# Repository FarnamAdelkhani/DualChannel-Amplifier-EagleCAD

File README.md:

# DualChannel-Amplifier-EagleCAD
Design amplifier design in Eagle, then export Gerber files for printing. Order components and solder away.

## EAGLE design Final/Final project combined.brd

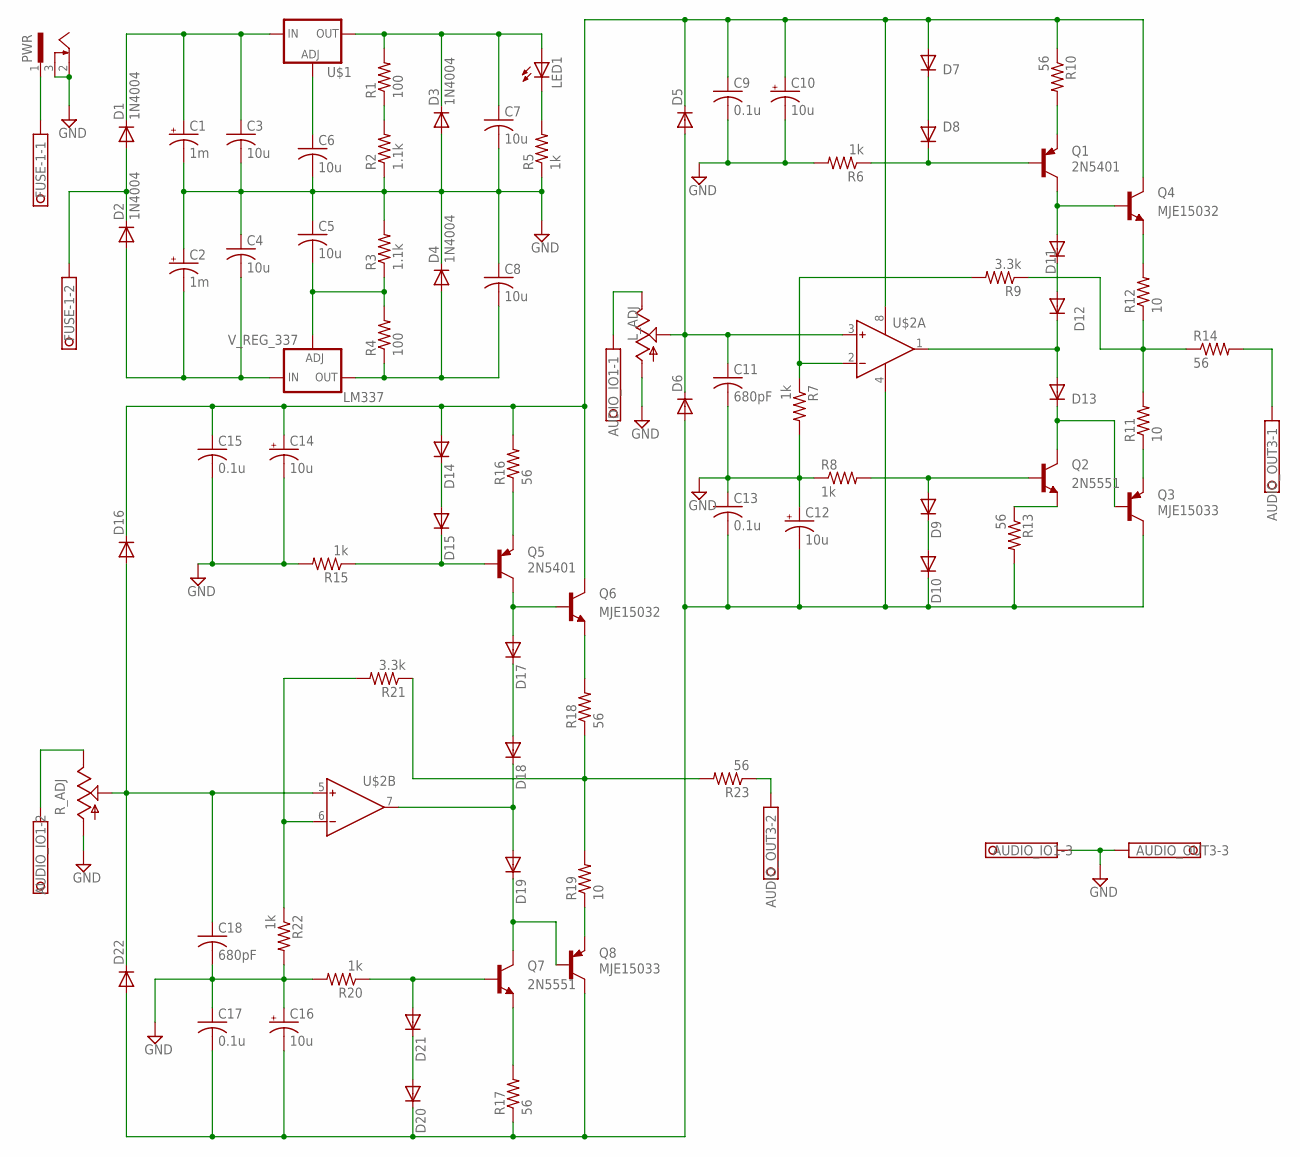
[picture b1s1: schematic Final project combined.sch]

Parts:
AUDIO_IO1: 1751251
AUDIO_OUT3: 1751251
C1, C2: 1m; E2-5
C3, C4, C5, C6, C7, C8: 10u; C025-024X044
C9, C13, C15, C17: 0.1u; C025-024X044
C10, C12, C14, C16: 10u; E2-5
C11, C18: 680pF; C025-024X044
D1, D2, D3, D4, D14, D15, D16, D17, D18, D19, D20, D21, D22: 1N4004; DO41-10
D5, D6, D7, D8, D9, D10, D11, D12, D13: 1N4148DO35-7; DO35-7
FUSE-1: 1751248
LED1: LED5MM
LM337: V_REG_337; TO220-ADJ-NEG
L_ADJ: TRIM_US-B64Y; B64Y
PWR: SCD-014A; SCD-014-A
Q1, Q5: 2N5401
Q2, Q7: 2N5551
Q3, Q8: MJE15033; TO220V
Q4, Q6: MJE15032; TO220V
R1, R4: 100; 0207/15
R2, R3: 1.1k; 0207/15
R5, R6, R7, R8, R15, R20, R22: 1k; 0207/15
R9, R21: 3.3k; 0207/15
R10, R13, R14, R16, R17, R18, R23: 56; 0207/15
R11, R12, R19: 10; 0207/15
R_ADJ: TRIM_US-B64Y; B64Y
U$1: V_REG_317SINK; TO220-ADJ
U$2: OP275'P'; DIL08

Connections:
GND: AUDIO_IO1.3, AUDIO_OUT3.3, C1.-, C2.+, C3.2, C4.1, C5.1, C6.2, C7.2, C8.1, C9.2, C10.-, C11.2, C12.+, C13.1, C14.-, C15.2, C16.+, C17.1, C18.2, D3.A, D4.C, L_ADJ.A, PWR.2, PWR.3, R2.1, R3.2, R5.1, R6.2, R7.2, R8.1, R15.2, R20.2, R22.2, R_ADJ.A
unnamed: D7.C, D8.A
unnamed: R1.1, R2.2
unnamed: C11.1, D5.A, D6.C, L_ADJ.S, U$2.3 (IN+)
unnamed: D11.A, Q1.C, Q4.1 (B)
unnamed: C9.1, C10.+, C14.+, C15.1, D5.C, D7.A, D14.A, D16.C, Q4.2 (C), Q6.2 (C), R10.1, R16.2, U$2.8 (V+)
unnamed: D11.C, D12.A
unnamed: D1.A, D2.C, FUSE-1.2
unnamed: D17.A, Q5.C, Q6.1 (B)
unnamed: C2.-, C4.2, D2.A, LM337.IN
unnamed: C1.+, C3.1, D1.C, U$1.IN
unnamed: D8.C, Q1.B, R6.1
unnamed: R7.1, R9.2, U$2.2 (IN-)
unnamed: D9.A, Q2.B, R8.2
unnamed: D9.C, D10.A
unnamed: Q2.E, R13.1
unnamed: D13.C, Q2.C, Q3.1 (B)
unnamed: D12.C, D13.A, U$2.1 (OUT)
unnamed: R9.1, R11.2, R12.1, R14.1
unnamed: Q3.3 (E), R11.1
unnamed: Q4.3 (E), R12.2
unnamed: C6.1, U$1.ADJ
unnamed: Q1.E, R10.2
unnamed: FUSE-1.1, PWR.1
unnamed: D14.C, D15.A
unnamed: D15.C, Q5.B, R15.1
unnamed: Q5.E, R16.1
unnamed: Q6.3 (E), R18.2
unnamed: D17.C, D18.A
unnamed: Q8.3 (E), R19.1
unnamed: D19.C, Q7.C, Q8.1 (B)
unnamed: D18.C, D19.A, U$2.7 (OUT)
unnamed: D21.A, Q7.B, R20.1
unnamed: D20.A, D21.C
unnamed: R18.1, R19.2, R21.1, R23.2
unnamed: R21.2, R22.1, U$2.6 (IN-)
unnamed: C18.1, D16.A, D22.C, R_ADJ.S, U$2.5 (IN+)
unnamed: Q7.E, R17.2
unnamed: AUDIO_IO1.2, R_ADJ.E
unnamed: C12.-, C13.2, C16.-, C17.2, D6.A, D10.C, D20.C, D22.A, Q3.2 (C), Q8.2 (C), R13.2, R17.1, U$2.4 (V-)
unnamed: AUDIO_IO1.1, L_ADJ.E
unnamed: C8.2, D4.A, LM337.OUT, R4.1
unnamed: C5.2, LM337.ADJ, R3.1, R4.2
unnamed: LED1.K (C), R5.2
unnamed: C7.1, D3.C, LED1.A, R1.2, U$1.OUT
unnamed: AUDIO_OUT3.2, R23.1
unnamed: AUDIO_OUT3.1, R14.2

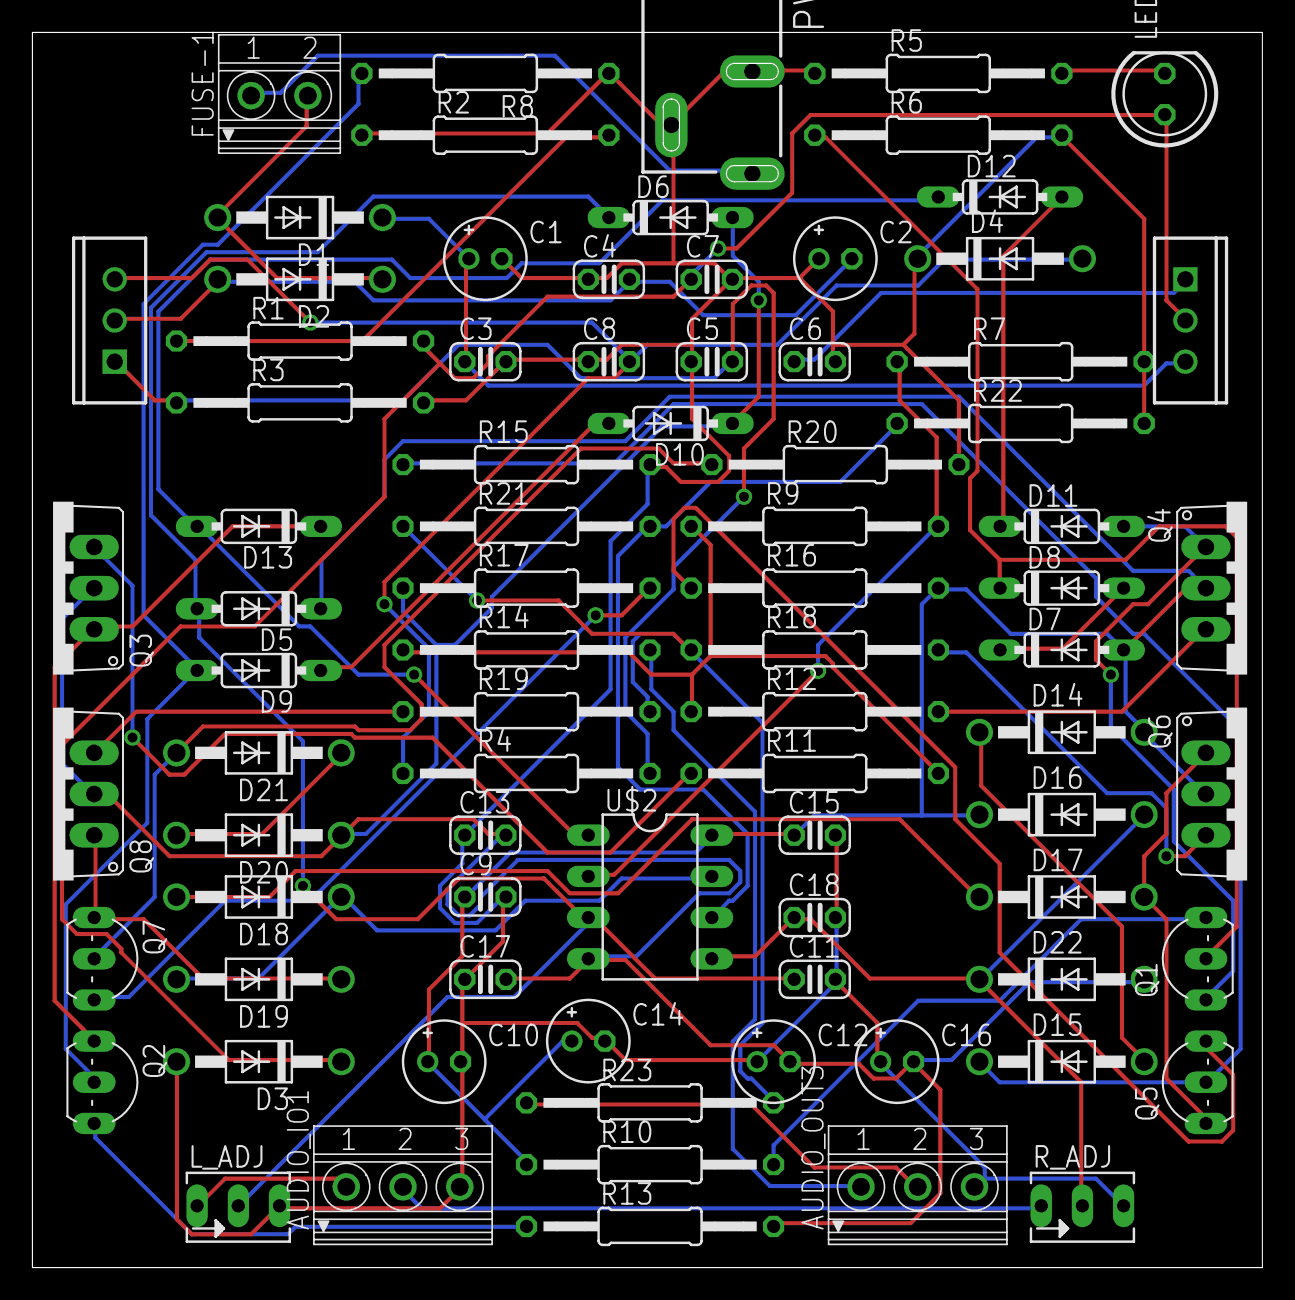
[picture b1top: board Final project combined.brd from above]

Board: 2 copper layers, 75.9 x 76.2 mm, 81 parts (0 on the bottom side), 47 nets.
